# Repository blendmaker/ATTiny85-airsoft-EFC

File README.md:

# Compact ATtiny85 Open-Source Airsoft EFC

An open-source, compact (~28 mm) Electronic Fire Control (EFC) and MOSFET board designed for Airsoft Automatic Electric Guns (AEGs). Designed completely in **KiCad** using open-source tools, this project aims to provide a reliable, high-performance, programmable DIY alternative to commercial MOSFET units.

---

## Key Features

* **Sensorless Cycle Detection:** Unlike standard EFC units that rely on delicate optical sensors or mechanical microswitches, this board performs cycle monitoring **without additional physical sensors**, minimizing internal moving parts and potential failure points.
* **Compact Round Design:** ~28 mm footprint tailored for tight spaces (e.g., buffer tubes or gearboxes).
* **High-Current Power Stage:** Engineered with massive copper traces, an active gate driver, and a low $R_{DS(on)}$ power MOSFET to easily handle peak motor currents (~40 A+).
* **100% Free & Open Source:** All schematics, PCB layouts, and firmware are freely available and built using open-source toolchains.

---

## Technical Specifications

| Component | Specification |
| :--- | :--- |
| **Microcontroller** | Microchip ATtiny85-20SU |
| **Gate Driver** | TC4428EOA (High-speed dual MOSFET driver) |
| **Power MOSFET** | IRFS7430TRLPBF ($1.3\text{ m}\Omega$, 40 V, D2PAK) |
| **Voltage Regulator** | HT7550-1 (5 V LDO, SOT-89) |
| **Freewheel Diode** | SS510 (5 A / 100 V Schottky) |
| **PCB Specs** | 2-layer, 28mm by 33mm size |

---

## Firmware & Flashing

* **Current Bootloader:** The current firmware revision utilizes the **Micronucleus bootloader** for flashing code via USB.
* **Roadmap Notice:** Future hardware and firmware revisions are planned to transition directly to an **ISP Programmer** interface via dedicated pogo-pin programming pads to maximize available flash memory and streamline assembly.

---

## Testing & Field Status

This hardware and firmware configuration is currently verified and field-tested under the following setups:

* **Gear Ratios:** Tested on **13:1** and **18:1** gear sets.
* **Power Source:** Tested exclusively with **2S LiPo** battery packs (7.4 V nominal / 8.4 V fully charged).

> **Note:** Testing for 3S LiPo (11.1 V) setups and ultra-high-speed gear ratios (e.g., DSG / 12:1) is planned for future iterations.

---

## Project Structure

```text
├── schematics/        # KiCad PCB layout (.kicad_pcb)
├── src/               # Platform.io & Ardnuino compatible ATtiny85 C++ source code
├── docs/              # TODO
└── README.md
```

---

## License

This project is licensed under the **MIT License** – feel free to modify, manufacture, and distribute for personal or commercial use.

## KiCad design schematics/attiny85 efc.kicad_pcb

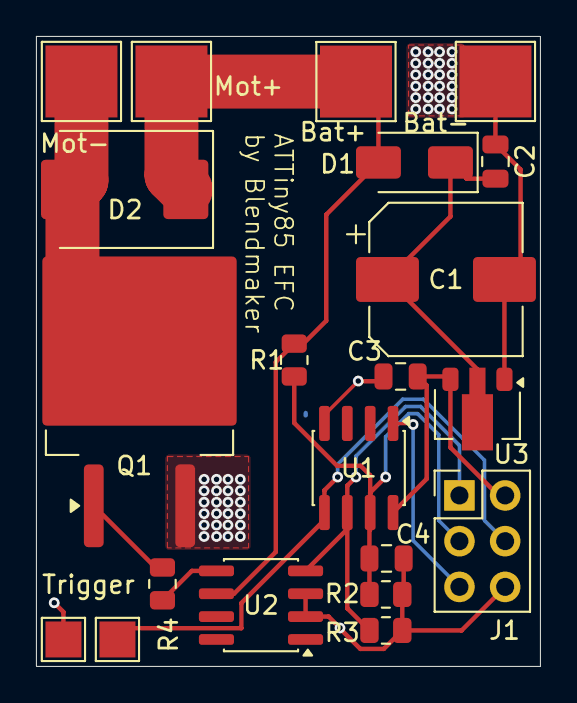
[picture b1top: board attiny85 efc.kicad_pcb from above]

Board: 2 copper layers, 28.0 x 35.0 mm, 21 parts (0 on the bottom side), 11 nets.

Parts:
Bat+: MOTOR_PLUS; TestPoint_Pad_4.0x4.0mm
Bat-: LIPO_MINUS; TestPoint_Pad_4.0x4.0mm
C1: 470uF; CP_Elec_8x10
C2, C3: 1uF; C_0805_2012Metric
C4: 4.7nF; C_0805_2012Metric
D1: 1N4007; D_SMA
D2: SR5100; D_SMC
J1: ISP_Pogo_Pads; PinHeader_2x03_P2.54mm_Vertical
Mot+: LIPO_PLUS; TestPoint_Pad_4.0x4.0mm
Mot-: MOTOR_MINUS; TestPoint_Pad_4.0x4.0mm
PAD_TRIG1: TRIGGER_A; TestPoint_Pad_2.0x2.0mm
Q1: IRFS3036; TO-263-2
R1: 47k; R_0805_2012Metric
R2, R3: 10k; R_0805_2012Metric
R4: 47R; R_0805_2012Metric
Trigger: TRIGGER_B; TestPoint_Pad_2.0x2.0mm
U1: ATtiny85-20SU; SOIC-8_3.9x4.9mm_P1.27mm
U2: TC4428EOA; SOIC-8_3.9x4.9mm_P1.27mm
U3: HT7550-1; SOT-89-3

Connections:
+5V: C3.1, J1.2, U1.8, U3.3
+BATT: Bat+.1, D1.2, D2.1, Mot+.1, R1.1, U2.6
GATE_DRV: R4.1, U2.5
GATE_FET: Q1.1, R4.2
GND: Bat-.1, C1.2, C2.2, C3.2, C4.2, J1.6, Q1.3, R2.2, R3.2, Trigger.1, U1.4, U2.2, U2.3, U3.1
MOTOR_MINUS: D2.2, Mot-.1, Q1.2
MOTOR_PB1: J1.1, R3.1, U1.6, U2.4
RESET_PB5: J1.5, U1.1
SENSE_PB2: C4.1, J1.3, R1.2, R2.1, U1.7
TRIGGER_PB0: J1.4, PAD_TRIG1.1, U1.5
V_LDO_IN: C1.1, C2.1, D1.1, U3.2
